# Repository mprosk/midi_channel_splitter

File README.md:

# MIDI Channel Splitter
Splits a MIDI connection into separate channels

Designed for installation into Hammond Mfg. 1455L801BK extruded enclosure

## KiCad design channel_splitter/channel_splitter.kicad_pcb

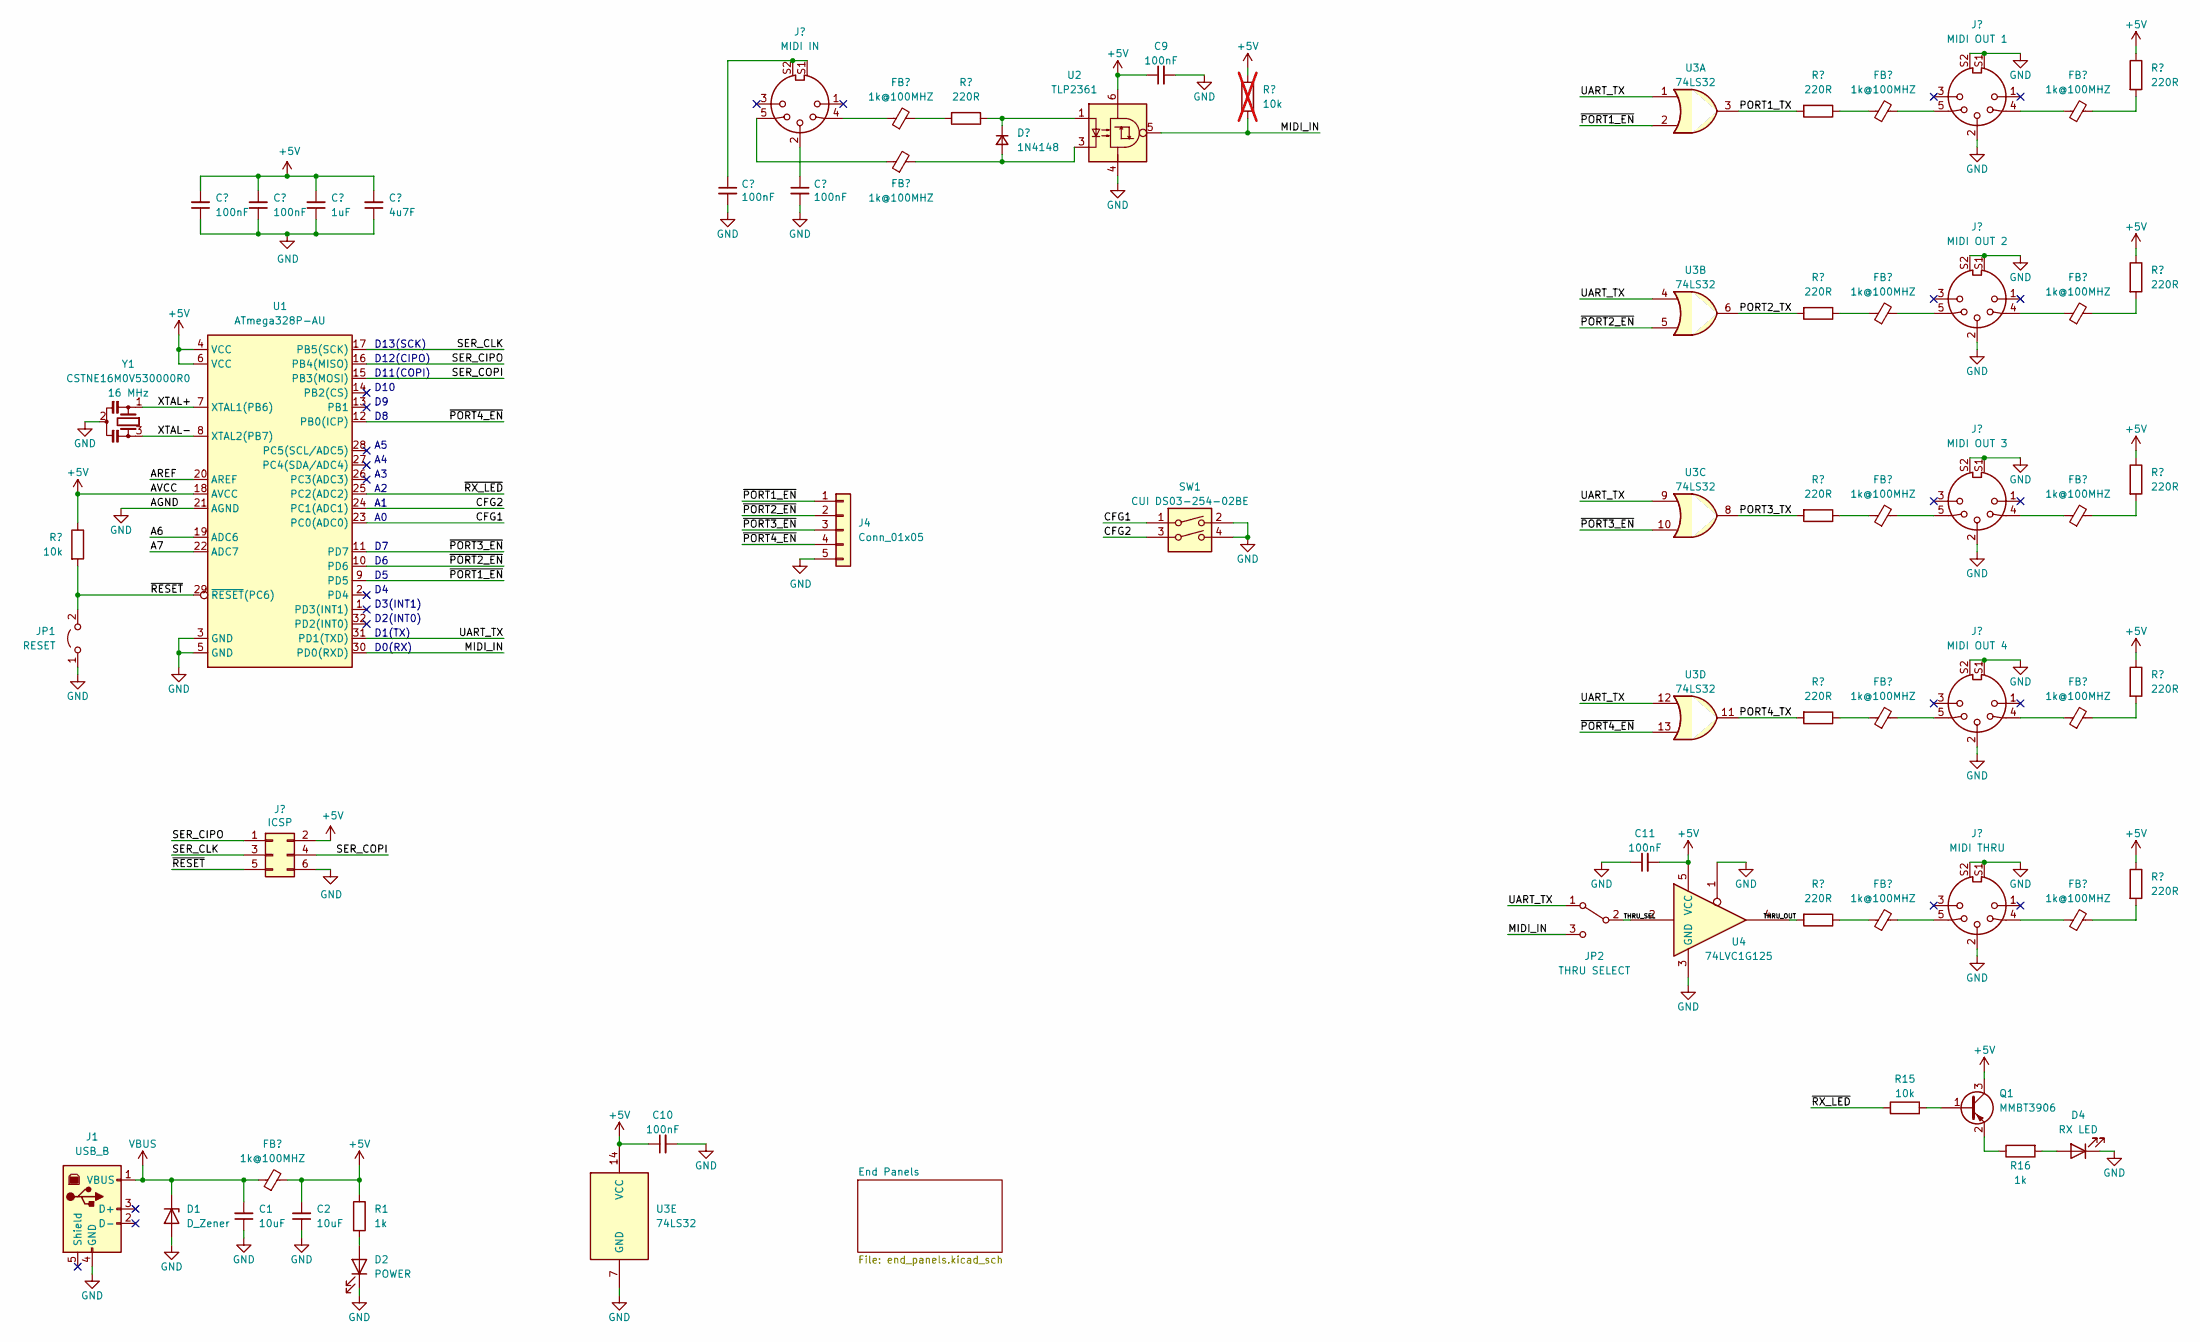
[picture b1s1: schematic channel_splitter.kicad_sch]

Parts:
C1, C2: 10uF; C_0805_2012Metric
C3, C4, C7, C8, C9, C10, C11: 100nF; C_0805_2012Metric
C5: 1uF; C_0805_2012Metric
C6: 4u7F; C_0805_2012Metric
D1: D_Zener; D_SOD-123
D2: POWER; LED_D3.0mm_Horizontal_O1.27mm_Z6.0mm
D3: 1N4148; D_SOD-123
D4: RX LED; LED_D3.0mm_Horizontal_O1.27mm_Z10.0mm
FB1, FB2, FB3, FB4, FB5, FB6, FB7, FB8, FB9, FB10, FB11, FB12, FB13: 1k@100MHZ; L_0805_2012Metric
J1: USB_B; USB_B_OST_USB-B1HSxx_Horizontal
J2: MIDI IN; CUI_SDS-50J
J3: ICSP; Tag-Connect_TC2030-IDC-NL_2x03_P1.27mm_Vertical
J4: Conn_01x05; PinHeader_1x05_P2.54mm_Vertical
J5: MIDI OUT 1; CUI_SDS-50J
J6: MIDI OUT 2; CUI_SDS-50J
J7: MIDI OUT 3; CUI_SDS-50J
J8: MIDI OUT 4; CUI_SDS-50J
J9: MIDI THRU; CUI_SDS-50J
JP1: RESET; PinHeader_1x02_P2.54mm_Vertical
JP2: THRU SELECT; PinHeader_1x03_P2.54mm_Vertical
Q1: MMBT3906; SOT-23
R1, R16: 1k; R_0805_2012Metric
R2, R15: 10k; R_0805_2012Metric
R3, R5, R6, R7, R8, R9, R10, R11, R12, R13, R14: 220R; R_0805_2012Metric
R4: 10k; R_0805_2012Metric; not fitted
SW1: CUI DS03-254-02BE; SW_DIP_CUI_DS03-254-02BE
U1: ATmega328P-AU; TQFP-32_7x7mm_P0.8mm
U2: TLP2361; SO-5_4.4x3.6mm_P1.27mm
U3: 74LS32; SOIC-14_3.9x8.7mm_P1.27mm
U4: 74LVC1G125; SOT-23-5
Y1: CSTNE16M0V530000R0; Resonator_SMD_Murata_CSTxExxV-3Pin_3.0x1.1mm

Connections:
+5V: C2.2, C3.2, C4.2, C5.2, C6.2, C9.1, C10.1, C11.2, FB1.2, J3.2, Q1.3 (C), R1.1, R2.1, R4.1, R6.1, R8.1, R10.1, R12.1, R14.1, U1.4 (VCC), U1.6 (VCC), U1.18 (AVCC), U2.6, U3.14 (VCC), U4.5 (VCC)
/A6: U1.19 (ADC6)
/A7: U1.22 (ADC7)
/AREF: U1.20 (AREF)
/CFG1: SW1.1, U1.23 (PC0(ADC0))
/CFG2: SW1.3, U1.24 (PC1(ADC1))
/MIDI_IN: JP2.3 (C), R4.2, U1.30 (PD0(RXD)), U2.5
/PORT1_TX: R5.2, U3.3
/PORT2_TX: R7.2, U3.6
/PORT3_TX: R9.2, U3.8
/PORT4_TX: R11.2, U3.11
/SER_CIPO: J3.1, U1.16 (PB4(MISO))
/SER_CLK: J3.3, U1.17 (PB5(SCK))
/SER_COPI: J3.4, U1.15 (PB3(MOSI))
/THRU_OUT: R13.2, U4.4
/THRU_SEL: JP2.2 (B), U4.2
/UART_TX: JP2.1 (A), U1.31 (PD1(TXD)), U3.1, U3.4, U3.9, U3.12
/XTAL+: U1.7 (XTAL1(PB6)), Y1.1
/XTAL-: U1.8 (XTAL2(PB7)), Y1.3
/~PORT1_EN: J4.1, U1.9 (PD5), U3.2
/~PORT2_EN: J4.2, U1.10 (PD6), U3.5
/~PORT3_EN: J4.3, U1.11 (PD7), U3.10
/~PORT4_EN: J4.4, U1.12 (PB0(ICP)), U3.13
/~RESET: J3.5, JP1.2 (B), R2.2, U1.29 (~RESET(PC6))
/~RX_LED: R15.1, U1.25 (PC2(ADC2))
GND: C1.1, C2.1, C3.1, C4.1, C5.1, C6.1, C7.2, C8.2, C9.2, C10.2, C11.1, D1.2 (A), D2.1 (K), D4.1 (K), J1.4 (GND), J3.6, J4.5, J5.2, J5.S1, J5.S2, J6.2, J6.S1, J6.S2, J7.2, J7.S1, J7.S2, J8.2, J8.S1, J8.S2, J9.2, J9.S1, J9.S2, JP1.1 (A), SW1.2, SW1.4, U1.3 (GND), U1.5 (GND), U1.21 (AGND), U2.4, U3.7 (GND), U4.1, U4.3 (GND), Y1.2
unnamed: C7.1, J2.S1, J2.S2
unnamed: C8.1, J2.2
unnamed: D2.2 (A), R1.2
unnamed: D3.2 (A), FB3.2, U2.3
unnamed: D3.1 (K), R3.1, U2.1
unnamed: D4.2 (A), R16.2
unnamed: FB2.1, J2.4
unnamed: FB2.2, R3.2
unnamed: FB3.1, J2.5
unnamed: FB4.1, R5.1
unnamed: FB4.2, J5.5
unnamed: FB5.1, J5.4
unnamed: FB5.2, R6.2
unnamed: FB6.1, R7.1
unnamed: FB6.2, J6.5
unnamed: FB7.1, J6.4
unnamed: FB7.2, R8.2
unnamed: FB8.1, R9.1
unnamed: FB8.2, J7.5
unnamed: FB9.1, J7.4
unnamed: FB9.2, R10.2
unnamed: FB10.1, R11.1
unnamed: FB10.2, J8.5
unnamed: FB11.1, J8.4
unnamed: FB11.2, R12.2
unnamed: FB12.1, R13.1
unnamed: FB12.2, J9.5
unnamed: FB13.1, J9.4
unnamed: FB13.2, R14.2
unnamed: Q1.1 (B), R15.2
unnamed: Q1.2 (E), R16.1
VBUS: C1.2, D1.1 (K), FB1.1, J1.1 (VBUS)

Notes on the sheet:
D12(CIPO)
D1(TX)
D3(INT1)
D11(COPI)
D0(RX)
D13(SCK)
D10
D2(INT0)

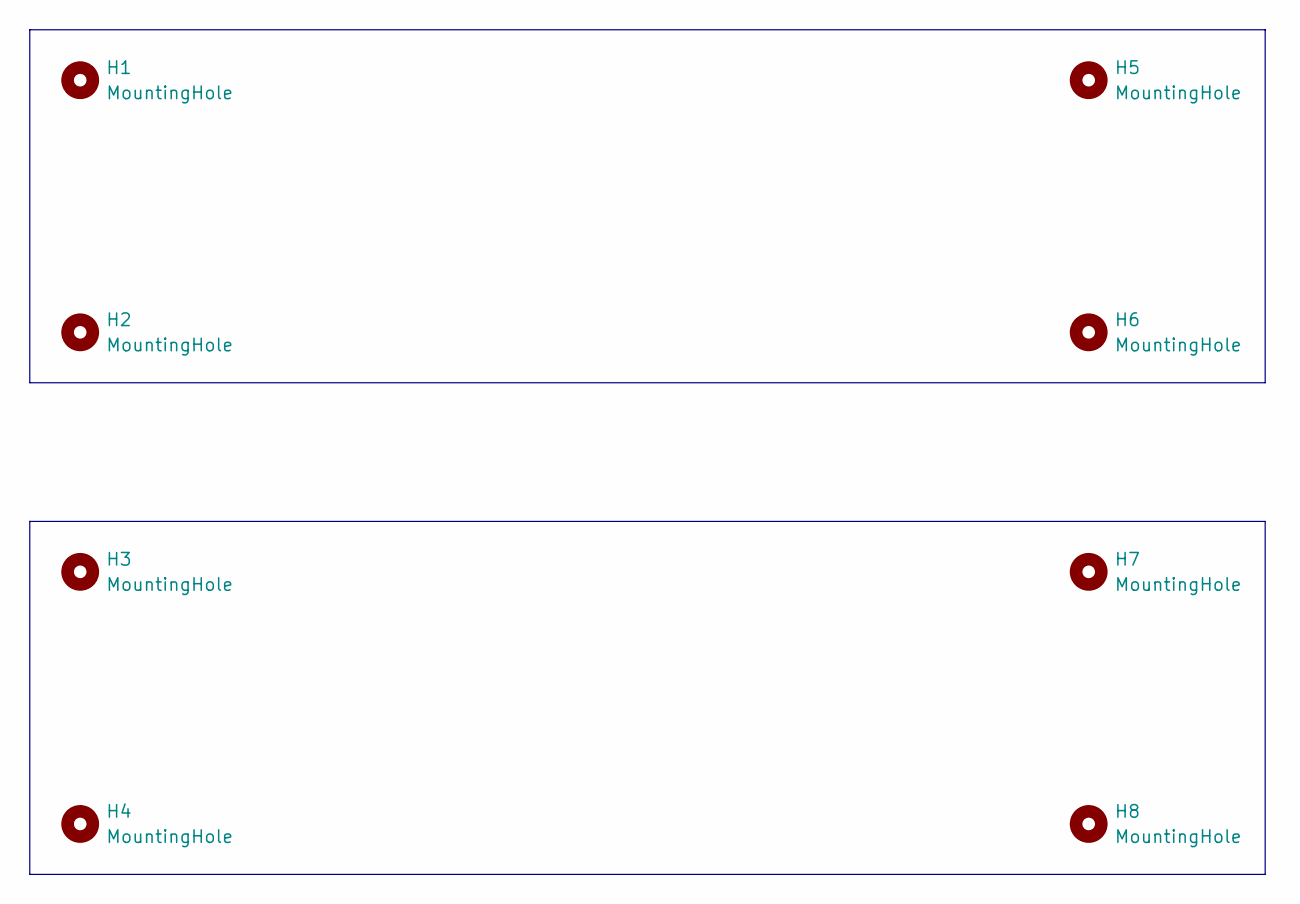
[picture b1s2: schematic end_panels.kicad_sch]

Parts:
H1, H2, H3, H4, H5, H6, H7, H8: MountingHole; Hammond_1455_End_Plate_Hole

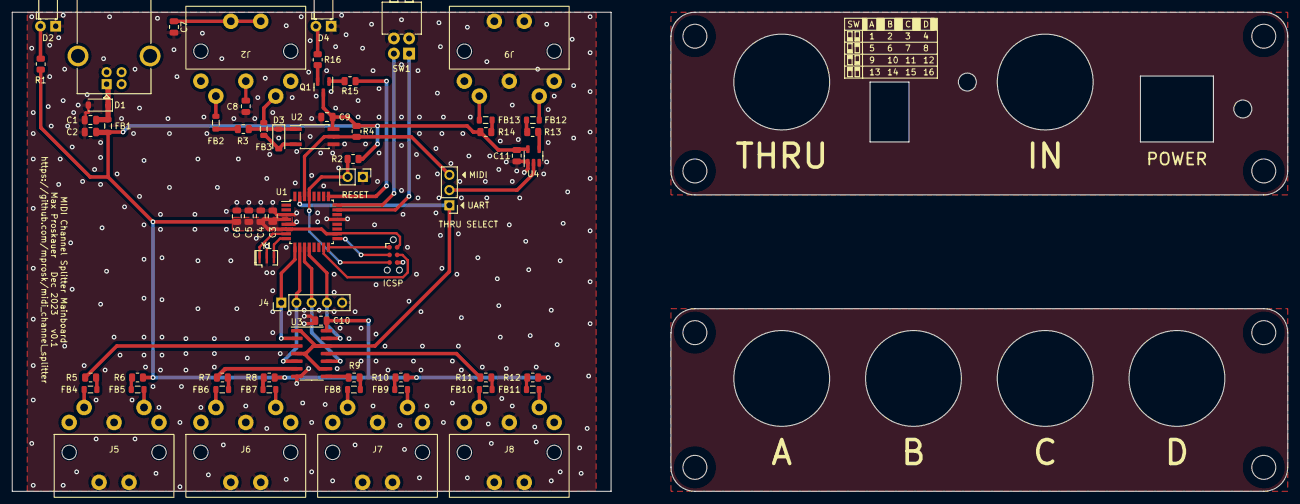
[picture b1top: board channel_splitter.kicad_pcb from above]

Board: 2 copper layers, 213.0 x 80.0 mm, 70 parts (0 on the bottom side), 55 nets.

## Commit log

2023-11-30 Add kosmo-lib
2023-12-17 Add simulation files
2023-12-17 Add datasheets
2023-12-17 Update to the latest kosmo-lib
2023-12-17 Update gitignore
2023-12-18 Get first pass schematic and layout
2023-12-18 Add gerbers
2023-12-18 Add version info to silkscreen. update gerbers
2024-01-07 Stub out firmware
2024-01-07 Finalize firmware
2024-01-08 Add pictures to the readme
2024-01-10 Misc local changes
